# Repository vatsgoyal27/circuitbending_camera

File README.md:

# Circuit Bending Setup

ESP32-S3-DevKitC-1 based circuit bending board with camera, TFT touchscreen display, SD card, I2S speaker amp, and analog microphone.

## Hardware

- **MCU:** ESP32-S3-DevKitC-1 (N16R8)
- **Camera:** OV2640 via 24-pin 1mm pitch FPC connector (J3)
- **Display:** TFT touchscreen (J4)
- **Storage:** MicroSD card (J27, Hirose DM3AT-SF-PEJM5)
- **Speaker amp:** MAX98357A I2S class D amp (U2)
- **Microphone:** MAX4466 analog mic preamp (U4)
- **Power:** IP2312 LiPo charger (U5) + MT3608 boost converter to 5V (U1)
- **LEDs:** 3x WS2812B addressable RGB (D5, D6, D7), daisy chained
- **Bend points:** Single pin 2.54mm headers throughout (J2, J5, J10–J26 etc.)

## Pin Map (WIll be updated and corrected soon)

### Camera (OV2640 DVP 8-bit)

| Signal | GPIO |
|---|---|
| xclk | 15 |
| pclk | 13 |
| vsync | 6 |
| href | 7 |
| d2 | 11 |
| d3 | 9 |
| d4 | 8 |
| d5 | 10 |
| d6 | 12 |
| d7 | 18 |
| d8 | 17 |
| d9 | 16 |
| sda (SCCB) | 4 |
| scl (SCCB) | 5 |

> pwdn and rstb are hardwired by R7/R8/R10, no GPIO needed.
> d0 and d1 are not connected (OV2640 outputs 8-bit only).

### Shared SPI Bus (TFT + touch + SD)

| Signal | GPIO |
|---|---|
| sck | 39 |
| mosi | 40 |
| miso | 41 |
| lcdcs | 42 |
| lcdrst | 38 |
| lcddc/rs | 47 |
| t_irq | 21 |
| sdcs | 43 |
| t_cs | 44 |

### I2S Amp (MAX98357A)

| Signal | GPIO |
|---|---|
| din | 2 |
| bclk | 14 |
| lrclk | 48 |

> sd_mode and gain are hardwired via R1, not software controlled.

### Microphone (MAX4466)

| Signal | GPIO |
|---|---|
| mic | 1 |

> Must be ADC1 (GPIO1-10) — ADC2 is unreliable with WiFi active.

### LEDs (WS2812B)

| Signal | GPIO |
|---|---|
| led_data | 0 |

> D5 → D6 → D7 daisy chained. One GPIO drives all three.

## Pins Avoided and Why

| GPIO | Reason |
|---|---|
| 3, 45, 46 | Strapping pins |
| 19, 20 | Native USB D-/D+ |
| 35, 36, 37 | Internally wired to octal PSRAM on N16R8 |

## Power

- Battery: 3.7V LiPo via JST PH 2.0mm (BT1)
- Charging: IP2312 module (U5) via USB-C
- 5V rail: MT3608 boost converter (U1) from battery
- 3.3V rail: onboard ESP32-S3 regulator
- 1.2V rail: NIC5365 LDO (U6) for camera
- 2.8V rail: MIC5504 LDO (U7) for camera

## Flashing

Flash and monitor over the **native USB port** (GPIO19/20, labeled "USB" on the DevKitC-1). Do not use the UART port (labeled "UART") — GPIO43/44 are repurposed for SPI chip selects and that port will show garbage. Select **USB CDC On Boot** in your build config.

## Built in KiCad
- KiCad E.D.A. 9.0.6

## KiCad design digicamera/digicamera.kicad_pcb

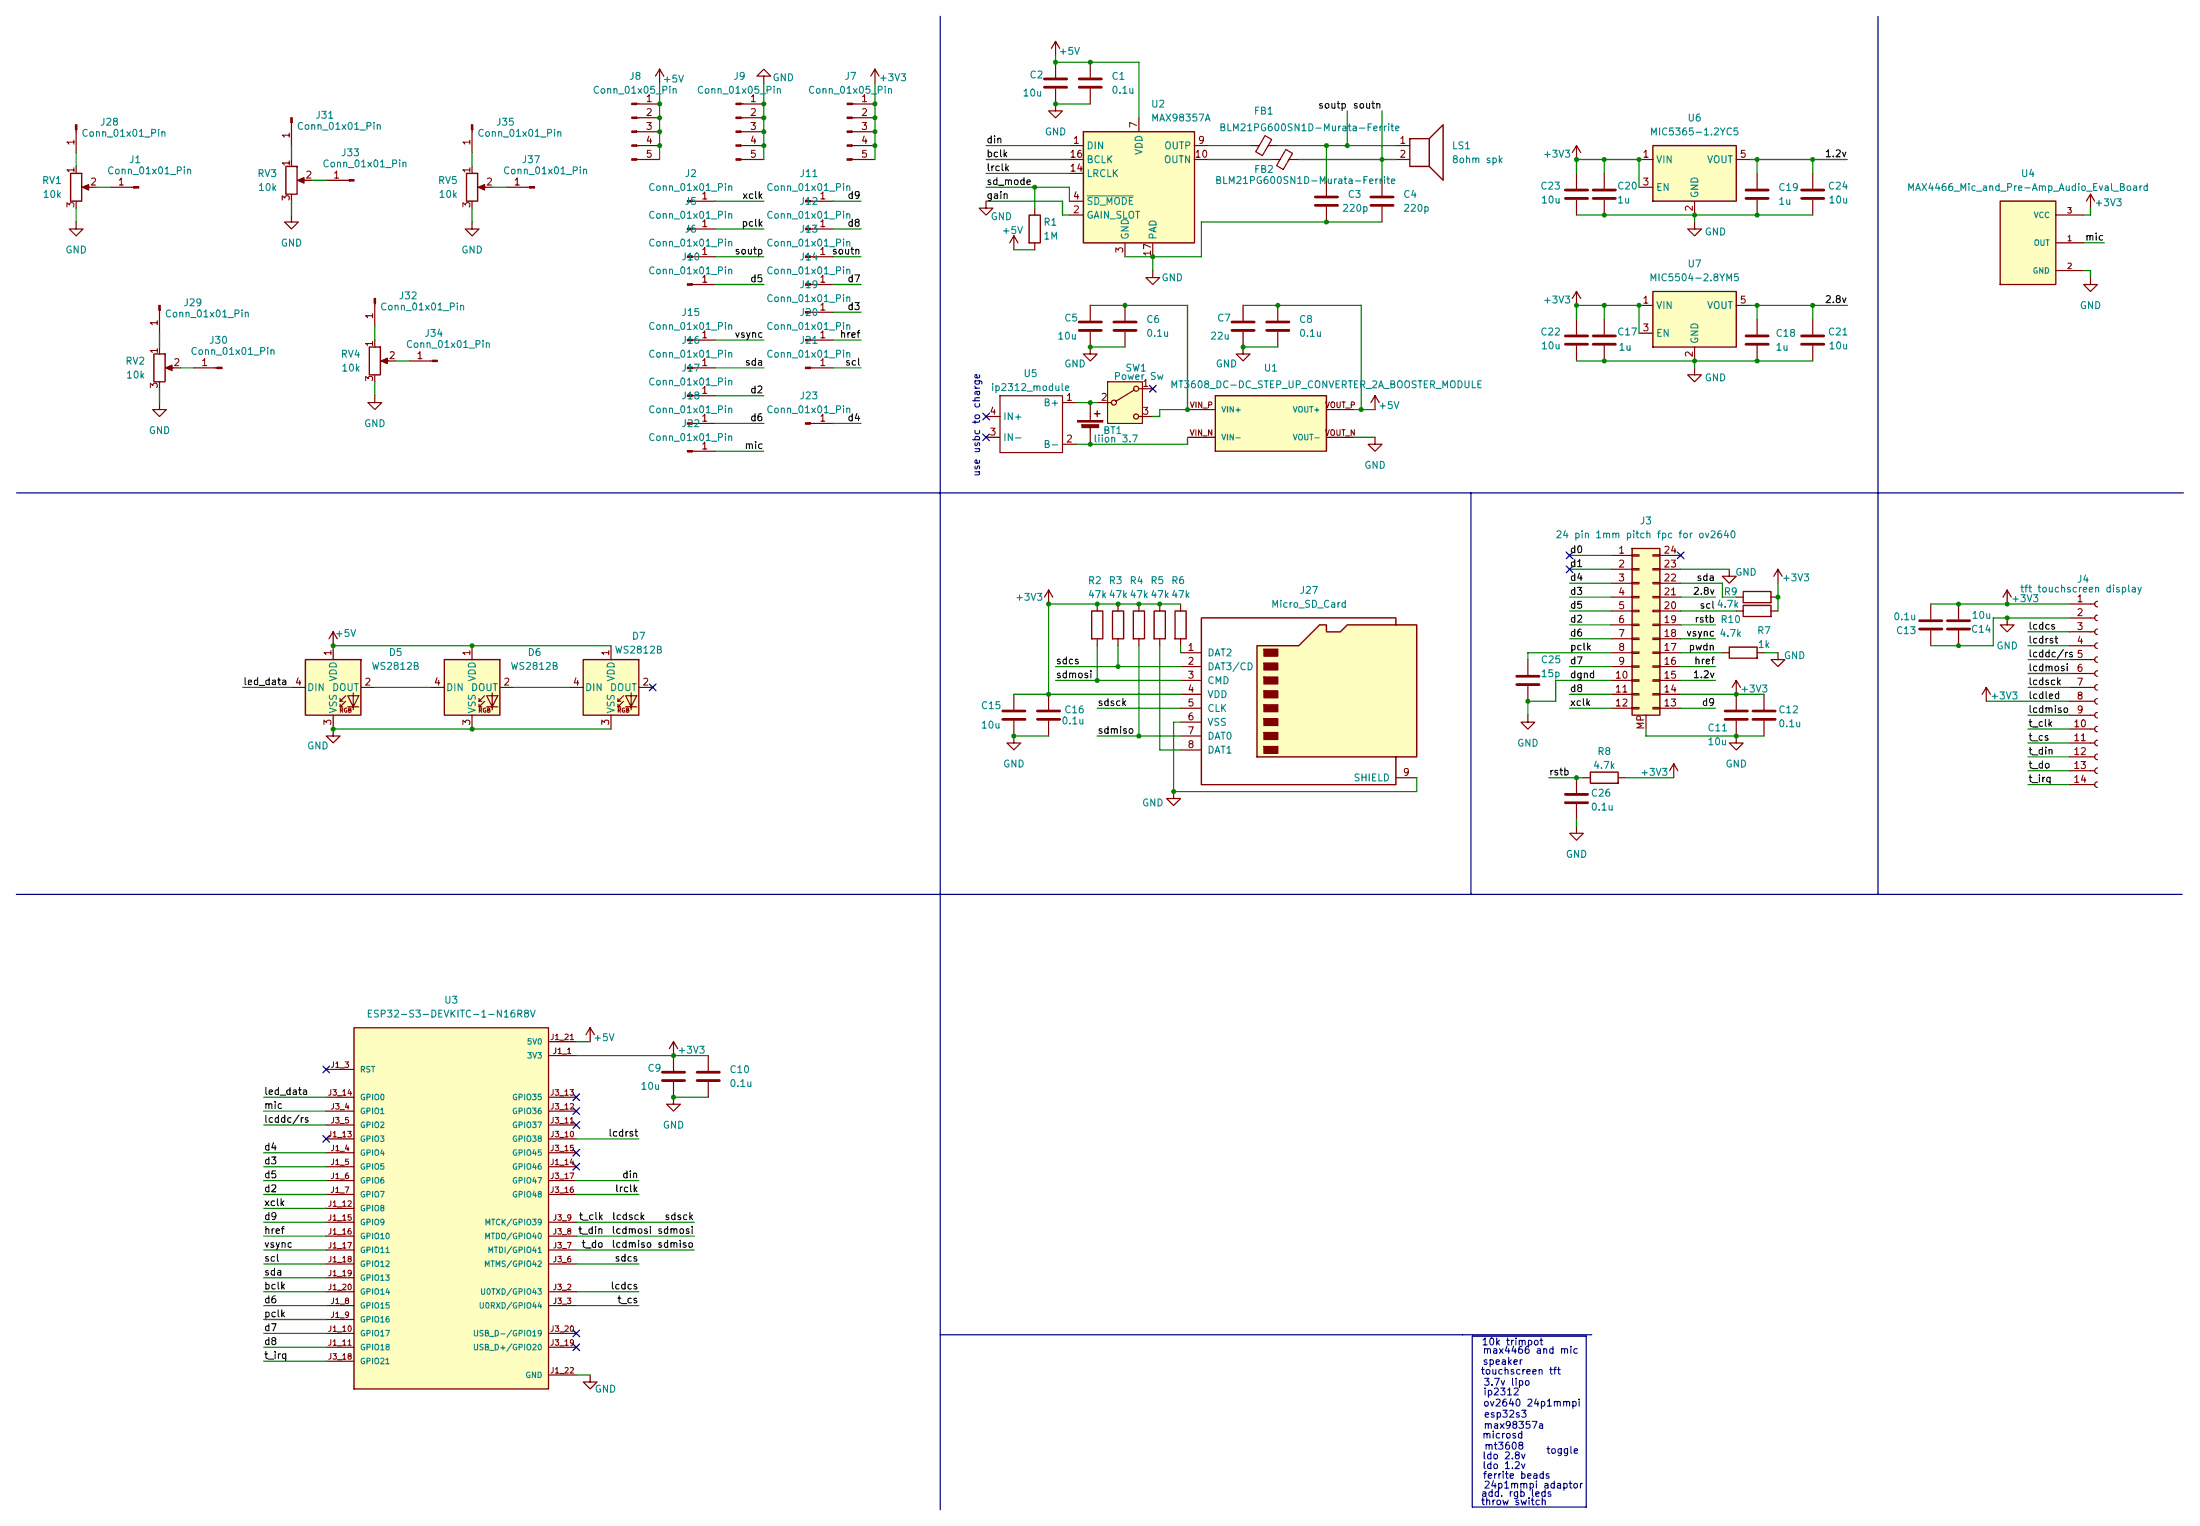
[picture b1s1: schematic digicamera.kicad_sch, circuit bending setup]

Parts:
BT1: liion 3.7; JST_PH_S2B-PH-K_1x02_P2.00mm_Horizontal
C1, C6, C8, C10, C12, C13, C16, C26: 0.1u; C_0805_2012Metric
C2, C5, C9, C11, C14, C15, C21, C22, C23, C24: 10u; C_0805_2012Metric
C3, C4: 220p; C_0805_2012Metric
C7: 22u; C_0805_2012Metric
C17, C18, C19, C20: 1u; C_0805_2012Metric
C25: 15p; C_0805_2012Metric
D5, D6, D7: WS2812B; LED_WS2812B_PLCC4_5.0x5.0mm_P3.2mm
FB1, FB2: BLM21PG600SN1D-Murata-Ferrite; BEADC2012X105N
J1, J2, J5, J6, J10, J11, J12, J13, J14, J15, J16, J17, J18, J19, J20, J21, J22, J23, J28, J29, J30, J31, J32, J33, J34, J35, J37: Conn_01x01_Pin; PinHeader_1x01_P2.54mm_Vertical
J3: 24 pin 1mm pitch fpc for ov2640; Molex_200528-0240_1x24-1MP_P1.00mm_Horizontal
J4: tft touchscreen display; PinHeader_1x14_P2.54mm_Vertical
J7, J8, J9: Conn_01x05_Pin; PinHeader_1x05_P2.54mm_Vertical
J27: Micro_SD_Card; microSD_HC_Hirose_DM3AT-SF-PEJM5
LS1: 8ohm spk; JST_PH_S2B-PH-K_1x02_P2.00mm_Horizontal
R1: 1M; R_0805_2012Metric
R2, R3, R4, R5, R6: 47k; R_0805_2012Metric
R7: 1k; R_0805_2012Metric
R8, R9, R10: 4.7k; R_0805_2012Metric
RV1, RV2, RV3, RV4, RV5: 10k; Potentiometer_Bourns_3386P_Vertical
SW1: Power Sw; RLS-102-F1-Toggle
U1: MT3608_DC-DC_STEP_UP_CONVERTER_2A_BOOSTER_MODULE; MODULE_MT3608_DC-DC_STEP_UP_CONVERTER_2A_BOOSTER_MODULE
U2: MAX98357A; QFN50P300X300X80-17N
U3: ESP32-S3-DEVKITC-1-N16R8V; XCVR_ESP32-S3-DEVKITC-1-N16R8V; PARTREV 1.1
U4: MAX4466_Mic_and_Pre-Amp_Audio_Eval_Board; MODULE_MAX4466_Microphone_Pre-Amp_Audio_Evaluation_Board; PARTREV 1.0
U5: ip2312_module; Untitled
U6: MIC5365-1.2YC5; SOT-353_SC-70-5
U7: MIC5504-2.8YM5; SOT-23-5

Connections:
+3V3: C9.1, C10.1, C11.1, C12.1, C13.2, C14.2, C15.1, C16.1, C17.1, C20.1, C22.1, C23.1, J3.14, J4.1, J4.8, J7.1, J7.2, J7.3, J7.4, J7.5, J27.4 (VDD), R2.1, R3.1, R4.1, R5.1, R6.1, R8.2, R9.2, R10.2, U3.J1_1 (3V3), U3.J1_2 (3V3), U4.3 (VCC), U6.1 (VIN), U6.3 (EN), U7.1 (VIN), U7.3 (EN)
+5V: C1.1, C2.1, C7.1, C8.1, D5.1 (VDD), D6.1 (VDD), D7.1 (VDD), J8.1, J8.2, J8.3, J8.4, J8.5, R1.2, U1.VOUT_P (VOUT+), U2.7 (VDD), U2.8 (VDD), U3.J1_21 (5V0)
/1.2v: C19.1, C24.1, J3.15, U6.5 (VOUT)
/2.8v: C18.1, C21.1, J3.21, U7.5 (VOUT)
/bclk: U2.16 (BCLK), U3.J1_20 (GPIO14)
/d0: J3.1
/d1: J3.2
/d2: J3.6, J17.1, U3.J1_7 (GPIO7)
/d3: J3.4, J19.1, U3.J1_5 (GPIO5)
/d4: J3.3, J23.1, U3.J1_4 (GPIO4)
/d5: J3.5, J10.1, U3.J1_6 (GPIO6)
/d6: J3.7, J18.1, U3.J1_8 (GPIO15)
/d7: J3.9, J14.1, U3.J1_10 (GPIO17)
/d8: J3.11, J12.1, U3.J1_11 (GPIO18)
/d9: J3.13, J11.1, U3.J1_15 (GPIO9)
/din: U2.1 (DIN), U3.J3_17 (GPIO47)
/href: J3.16, J20.1, U3.J1_16 (GPIO10)
/lcdcs: J4.3, U3.J3_2 (U0TXD/GPIO43)
/lcddc/rs: J4.5, U3.J3_5 (GPIO2)
/lcdmiso: J4.9, J4.13, J27.7 (DAT0), R4.2, U3.J3_7 (MTDI/GPIO41)
/lcdmosi: J4.6, J4.12, J27.3 (CMD), R2.2, U3.J3_8 (MTDO/GPIO40)
/lcdrst: J4.4, U3.J3_10 (GPIO38)
/lcdsck: J4.7, J4.10, J27.5 (CLK), U3.J3_9 (MTCK/GPIO39)
/led_data: D5.4 (DIN), U3.J3_14 (GPIO0)
/lrclk: U2.14 (LRCLK), U3.J3_16 (GPIO48)
/mic: J22.1, U3.J3_4 (GPIO1), U4.1 (OUT)
/pclk: C25.1, J3.8, J5.1, U3.J1_9 (GPIO16)
/pwdn: J3.17, R7.1
/rstb: C26.1, J3.19, R8.1
/scl: J3.20, J21.1, R10.1, U3.J1_18 (GPIO12)
/sd_mode: R1.1, U2.4 (~SD_MODE)
/sda: J3.22, J16.1, R9.1, U3.J1_19 (GPIO13)
/sdcs: J27.2 (DAT3/CD), R3.2, U3.J3_6 (MTMS/GPIO42)
/soutn: C4.1, FB2.2, J13.1, LS1.2
/soutp: C3.1, FB1.2, J6.1, LS1.1
/t_cs: J4.11, U3.J3_3 (U0RXD/GPIO44)
/t_irq: J4.14, U3.J3_18 (GPIO21)
/vsync: J3.18, J15.1, U3.J1_17 (GPIO11)
/xclk: J2.1, J3.12, U3.J1_12 (GPIO8)
GND: C1.2, C2.2, C3.2, C4.2, C5.2, C6.2, C7.2, C8.2, C9.2, C10.2, C11.2, C12.2, C13.1, C14.1, C15.2, C16.2, C17.2, C18.2, C19.2, C20.2, C21.2, C22.2, C23.2, C24.2, C25.2, C26.2, D5.3 (VSS), D6.3 (VSS), D7.3 (VSS), J3.10, J3.23, J3.MP, J4.2, J9.1, J9.2, J9.3, J9.4, J9.5, J27.6 (VSS), J27.9 (SHIELD), R7.2, RV1.3, RV2.3, RV3.3, RV4.3, RV5.3, U1.VOUT_N (VOUT-), U2.2 (GAIN_SLOT), U2.3 (GND), U2.11 (GND), U2.15 (GND), U2.17 (PAD), U3.J1_22 (GND), U3.J3_1 (GND), U3.J3_21 (GND), U3.J3_22 (GND), U4.2 (GND), U6.2 (GND), U7.2 (GND)
unnamed: BT1.1 (+), SW1.2 (B), U5.1 (B+)
unnamed: BT1.2 (-), U1.VIN_N (VIN-), U5.2 (B-)
unnamed: D5.2 (DOUT), D6.4 (DIN)
unnamed: D6.2 (DOUT), D7.4 (DIN)
unnamed: J1.1, RV1.2
unnamed: J27.8 (DAT1), R5.2
unnamed: J27.1 (DAT2), R6.2
unnamed: J28.1, RV1.1
unnamed: J29.1, RV2.1
unnamed: J30.1, RV2.2
unnamed: J31.1, RV3.1
unnamed: J32.1, RV4.1
unnamed: J33.1, RV3.2
unnamed: J34.1, RV4.2
unnamed: J35.1, RV5.1
unnamed: J37.1, RV5.2
unnamed: C5.1, C6.1, SW1.3 (C), U1.VIN_P (VIN+)
unnamed: FB2.1, U2.10 (OUTN)
unnamed: FB1.1, U2.9 (OUTP)

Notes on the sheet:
ov2640 24p1mmpi
microsd
throw switch
ldo 1.2v
use usbc to charge
ip2312
ferrite beads
toggle
mt3608
10k trimpot
3.7v lipo
speaker
max98357a
ldo 2.8v
24p1mmpi adaptor
max4466 and mic
touchscreen tft
add. rgb leds
esp32s3

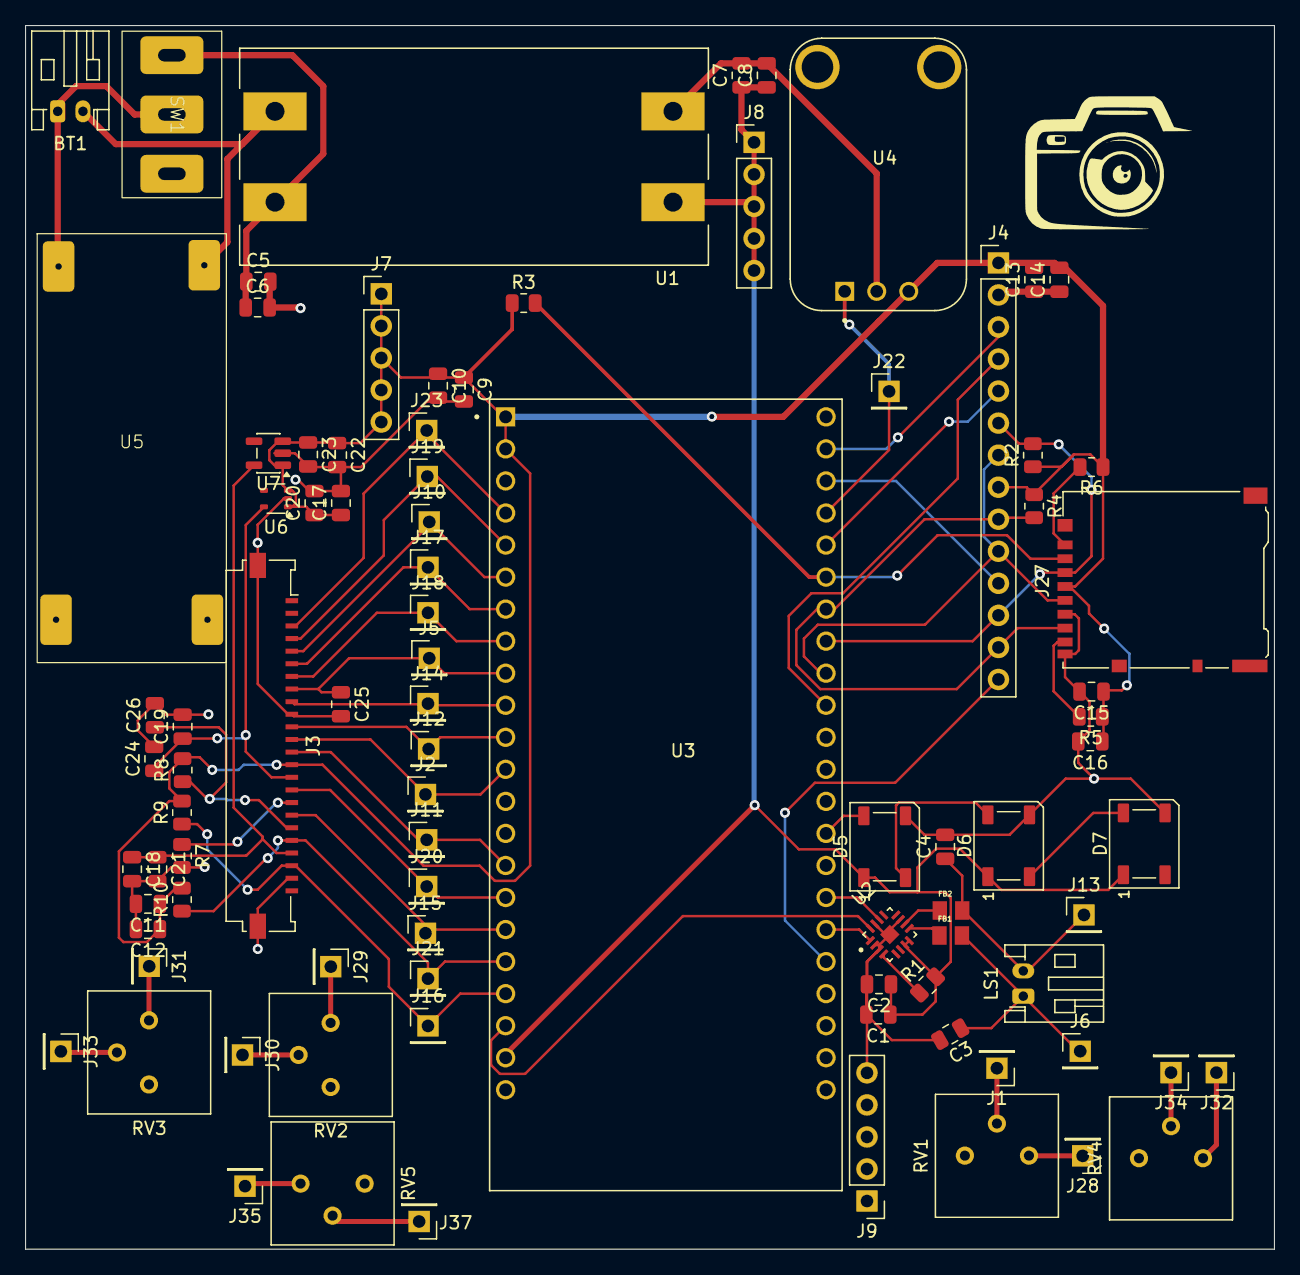
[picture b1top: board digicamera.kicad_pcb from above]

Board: 2 copper layers, 99.0 x 97.0 mm, 89 parts (0 on the bottom side), 57 nets.

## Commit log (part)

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2026-06-28 kicad schematic
    in progress
